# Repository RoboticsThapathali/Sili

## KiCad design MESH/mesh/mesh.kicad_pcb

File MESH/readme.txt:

//document created on 2019/20

contains two pcb layout
one of nano and other of arduino uno 
uno was tested 
but nano needs to be tested

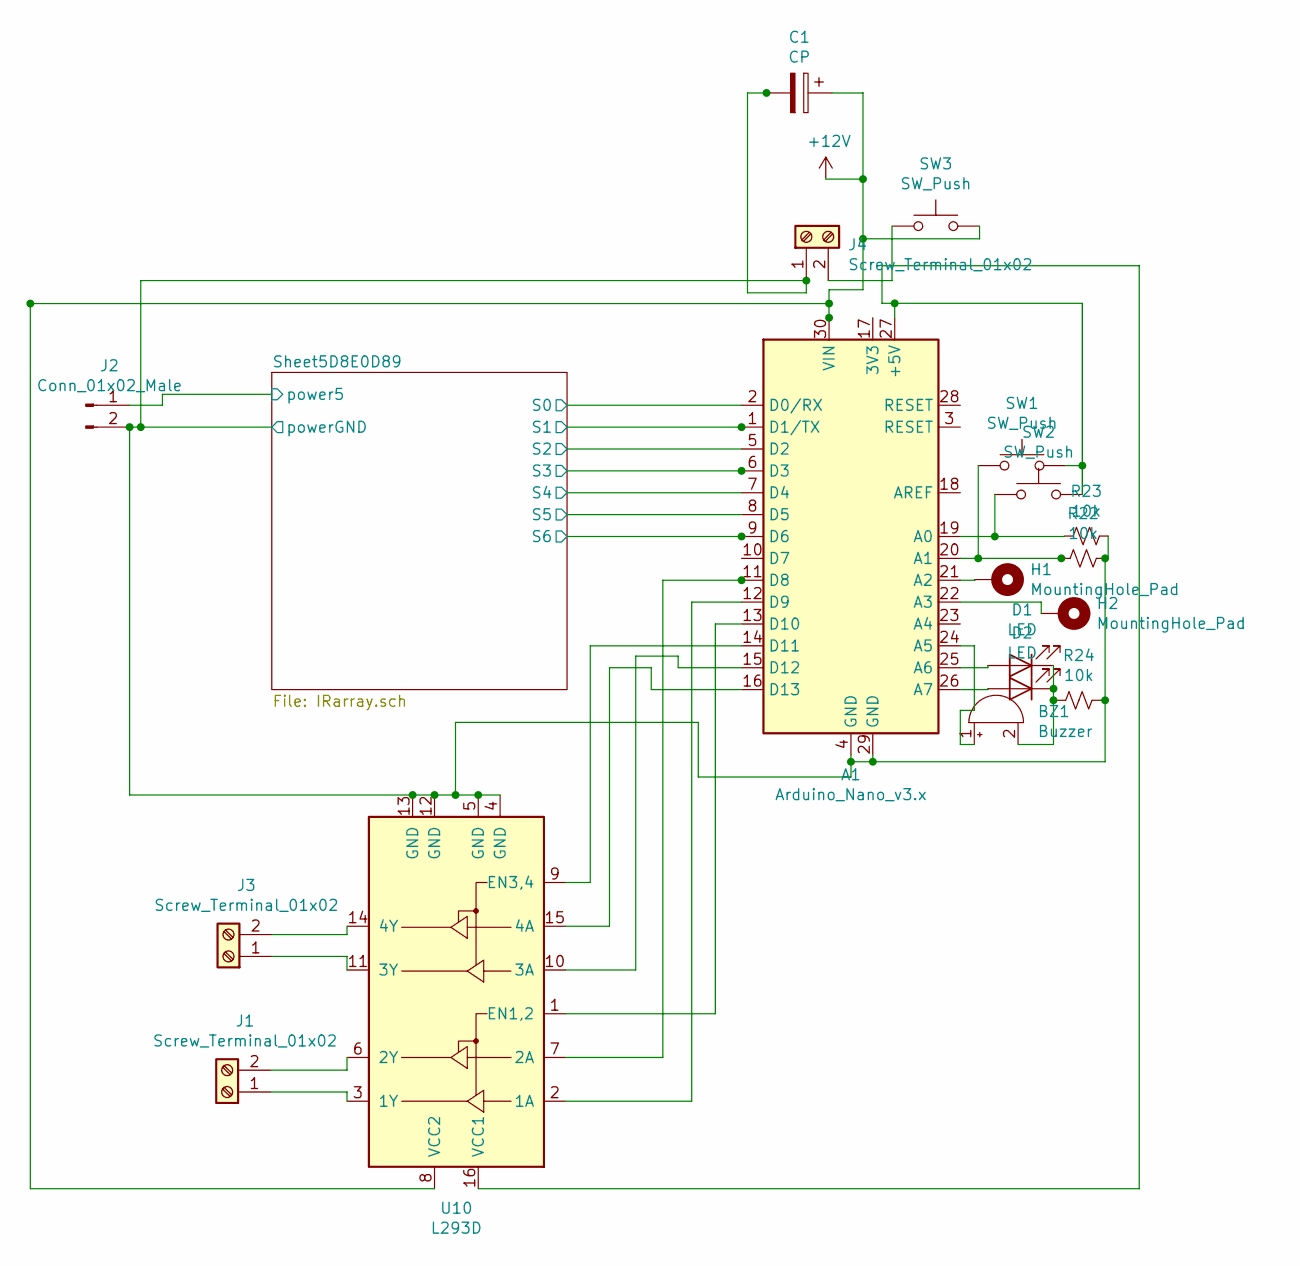
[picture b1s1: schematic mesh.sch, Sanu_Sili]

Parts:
A1: Arduino_Nano_v3.x; Arduino_Nano
BZ1: Buzzer; Buzzer_12x9.5RM7.6
C1: CP; CP_Radial_D8.0mm_P3.80mm
D1, D2: LED; LED_D5.0mm
H1, H2: MountingHole_Pad; MountingHole_4mm_Pad
J1, J3, J4: Screw_Terminal_01x02; TerminalBlock_Phoenix_MKDS-1,5-2-5.08_1x02_P5.08mm_Horizont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
J2: Conn_01x02_Male; PinHeader_1x02_P2.54mm_Vertical
R22, R23, R24: 10k; R_Axial_DIN0207_L6.3mm_D2.5mm_P7.62mm_Horizontal
SW1, SW2, SW3: SW_Push; SW_PUSH_6mm
U10: L293D; DIP-16_W7.62mm

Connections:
+12V: A1.30 (VIN), C1.1, SW3.2, U10.8 (VCC2)
/Sheet5D8E0D89/S0: A1.2 (D0/RX); also elsewhere on the board
/Sheet5D8E0D89/S1: A1.1 (D1/TX); also elsewhere on the board
/Sheet5D8E0D89/S2: A1.5 (D2); also elsewhere on the board
/Sheet5D8E0D89/S3: A1.6 (D3); also elsewhere on the board
/Sheet5D8E0D89/S4: A1.7 (D4); also elsewhere on the board
/Sheet5D8E0D89/S5: A1.8 (D5); also elsewhere on the board
/Sheet5D8E0D89/S6: A1.9 (D6); also elsewhere on the board
/Sheet5D8E0D89/power5: J2.1; also elsewhere on the board
/Sheet5D8E0D89/powerGND: A1.4 (GND), A1.29 (GND), C1.2, J2.2, J4.1, R22.1, R23.1, R24.1, U10.4 (GND), U10.5 (GND), U10.12 (GND), U10.13 (GND); also elsewhere on the board
unnamed: A1.11 (D8), U10.7 (2A)
unnamed: A1.12 (D9), U10.2 (1A)
unnamed: A1.13 (D10), U10.1 (EN1,2)
unnamed: A1.14 (D11), U10.9 (EN3,4)
unnamed: A1.15 (D12), U10.10 (3A)
unnamed: A1.16 (D13), U10.15 (4A)
unnamed: A1.19 (A0), R23.2, SW2.1
unnamed: A1.20 (A1), R22.2, SW1.1
unnamed: A1.21 (A2), H1.1
unnamed: A1.22 (A3), H2.1
unnamed: A1.24 (A5), BZ1.1 (-)
unnamed: A1.25 (A6), D1.2 (A)
unnamed: A1.26 (A7), D2.2 (A)
unnamed: A1.27 (+5V), SW1.2, SW2.2, U10.16 (VCC1)
unnamed: BZ1.2 (+), D1.1 (K), D2.1 (K), R24.2
unnamed: J1.1, U10.3 (1Y)
unnamed: J1.2, U10.6 (2Y)
unnamed: J3.1, U10.11 (3Y)
unnamed: J3.2, U10.14 (4Y)
unnamed: J4.2, SW3.1

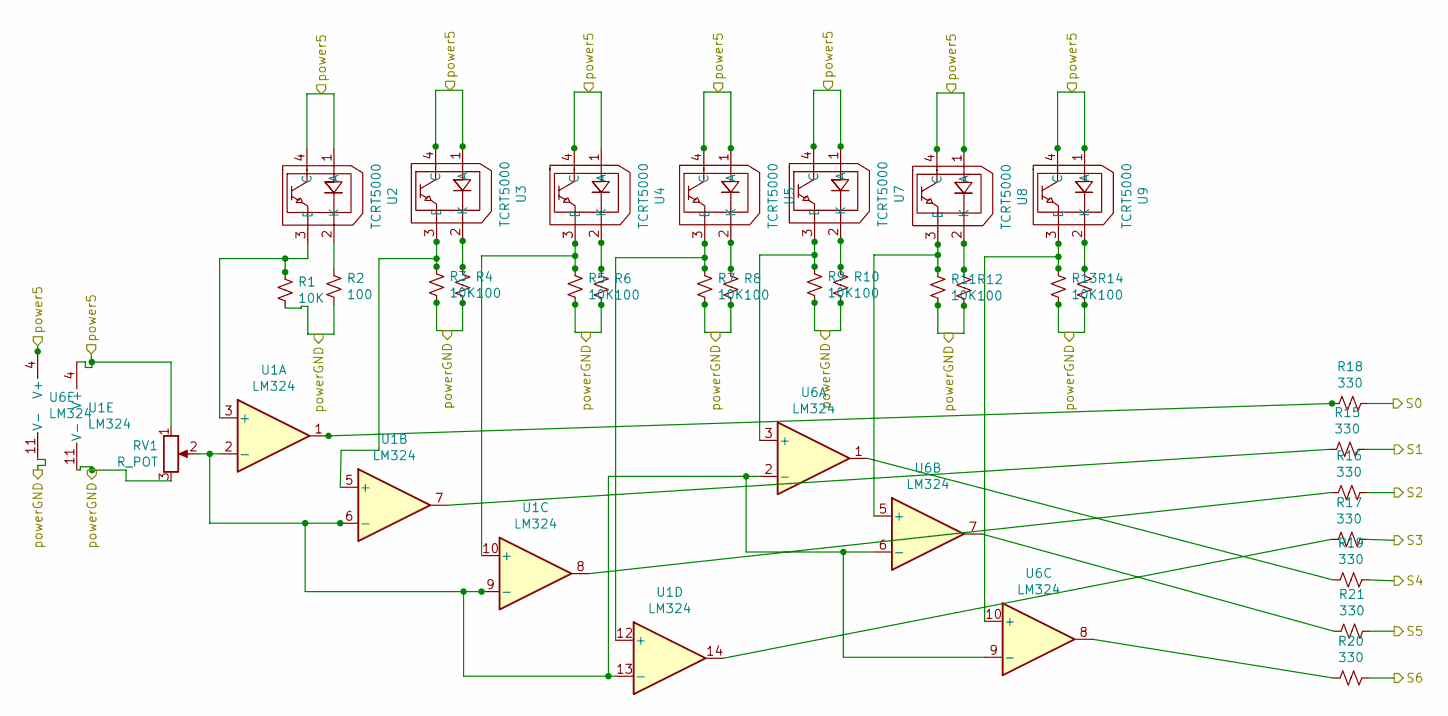
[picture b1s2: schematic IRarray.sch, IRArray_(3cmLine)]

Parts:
R1, R3, R5, R7, R9, R11, R13: 10K; R_Axial_DIN0207_L6.3mm_D2.5mm_P7.62mm_Horizontal
R2, R4, R6, R8, R10, R12, R14: 100; R_Axial_DIN0207_L6.3mm_D2.5mm_P7.62mm_Horizontal
R15, R16, R17, R18, R19, R20, R21: 330; R_Axial_DIN0207_L6.3mm_D2.5mm_P7.62mm_Horizontal
RV1: R_POT; Potentiometer_Runtron_RM-065_Vertical
U1, U6: LM324; DIP-14_W7.62mm
U2, U3, U4, U5, U7, U8, U9: TCRT5000; TCRT 5000

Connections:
/Sheet5D8E0D89/S0: R18.1; also elsewhere on the board
/Sheet5D8E0D89/S1: R15.1; also elsewhere on the board
/Sheet5D8E0D89/S2: R16.1; also elsewhere on the board
/Sheet5D8E0D89/S3: R17.1; also elsewhere on the board
/Sheet5D8E0D89/S4: R19.1; also elsewhere on the board
/Sheet5D8E0D89/S5: R21.1; also elsewhere on the board
/Sheet5D8E0D89/S6: R20.1; also elsewhere on the board
/Sheet5D8E0D89/power5: RV1.1, U1.4 (V+), U2.1 (A), U2.4 (C), U3.1 (A), U3.4 (C), U4.1 (A), U4.4 (C), U5.1 (A), U5.4 (C), U6.4 (V+), U7.1 (A), U7.4 (C), U8.1 (A), U8.4 (C), U9.1 (A), U9.4 (C); also elsewhere on the board
/Sheet5D8E0D89/powerGND: R1.2, R2.2, R3.2, R4.2, R5.2, R6.2, R7.2, R8.2, R9.2, R10.2, R11.2, R12.2, R13.2, R14.2, RV1.3, U1.11 (V-), U6.11 (V-); also elsewhere on the board
unnamed: R1.1, U1.3 (+), U2.3 (E)
unnamed: R2.1, U2.2 (K)
unnamed: R3.1, U1.5 (+), U3.3 (E)
unnamed: R4.1, U3.2 (K)
unnamed: R5.1, U1.10 (+), U4.3 (E)
unnamed: R6.1, U4.2 (K)
unnamed: R7.1, U1.12 (+), U5.3 (E)
unnamed: R8.1, U5.2 (K)
unnamed: R9.1, U6.3 (+), U7.3 (E)
unnamed: R10.1, U7.2 (K)
unnamed: R11.1, U6.5 (+), U8.3 (E)
unnamed: R12.1, U8.2 (K)
unnamed: R13.1, U6.10 (+), U9.3 (E)
unnamed: R14.1, U9.2 (K)
unnamed: R15.2, U1.7
unnamed: R16.2, U1.8
unnamed: R17.2, U1.14
unnamed: R18.2, U1.1
unnamed: R19.2, U6.1
unnamed: R20.2, U6.8
unnamed: R21.2, U6.7
unnamed: RV1.2, U1.2 (-), U1.6 (-), U1.9 (-), U1.13 (-), U6.2 (-), U6.6 (-), U6.9 (-)

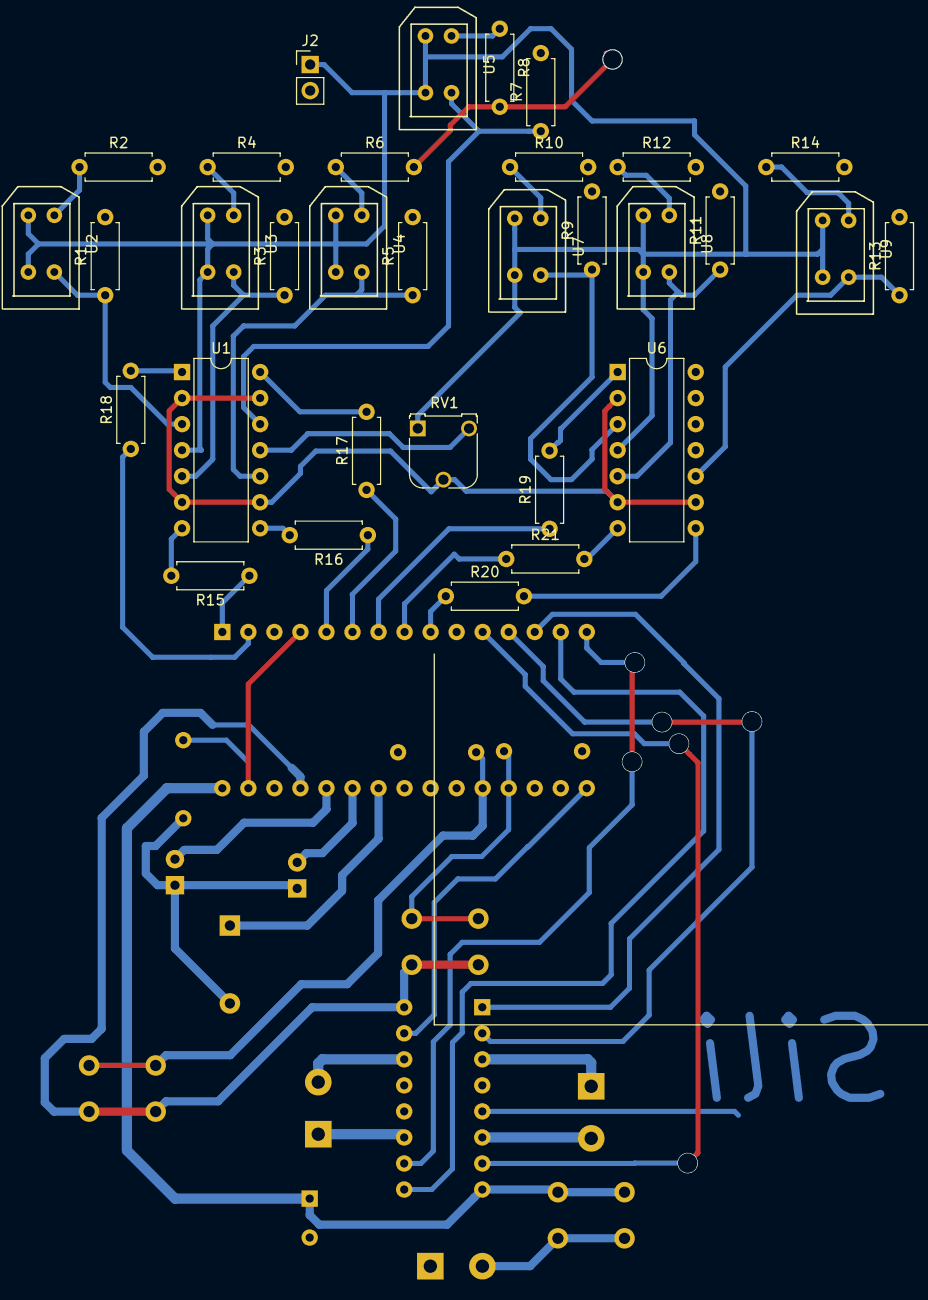
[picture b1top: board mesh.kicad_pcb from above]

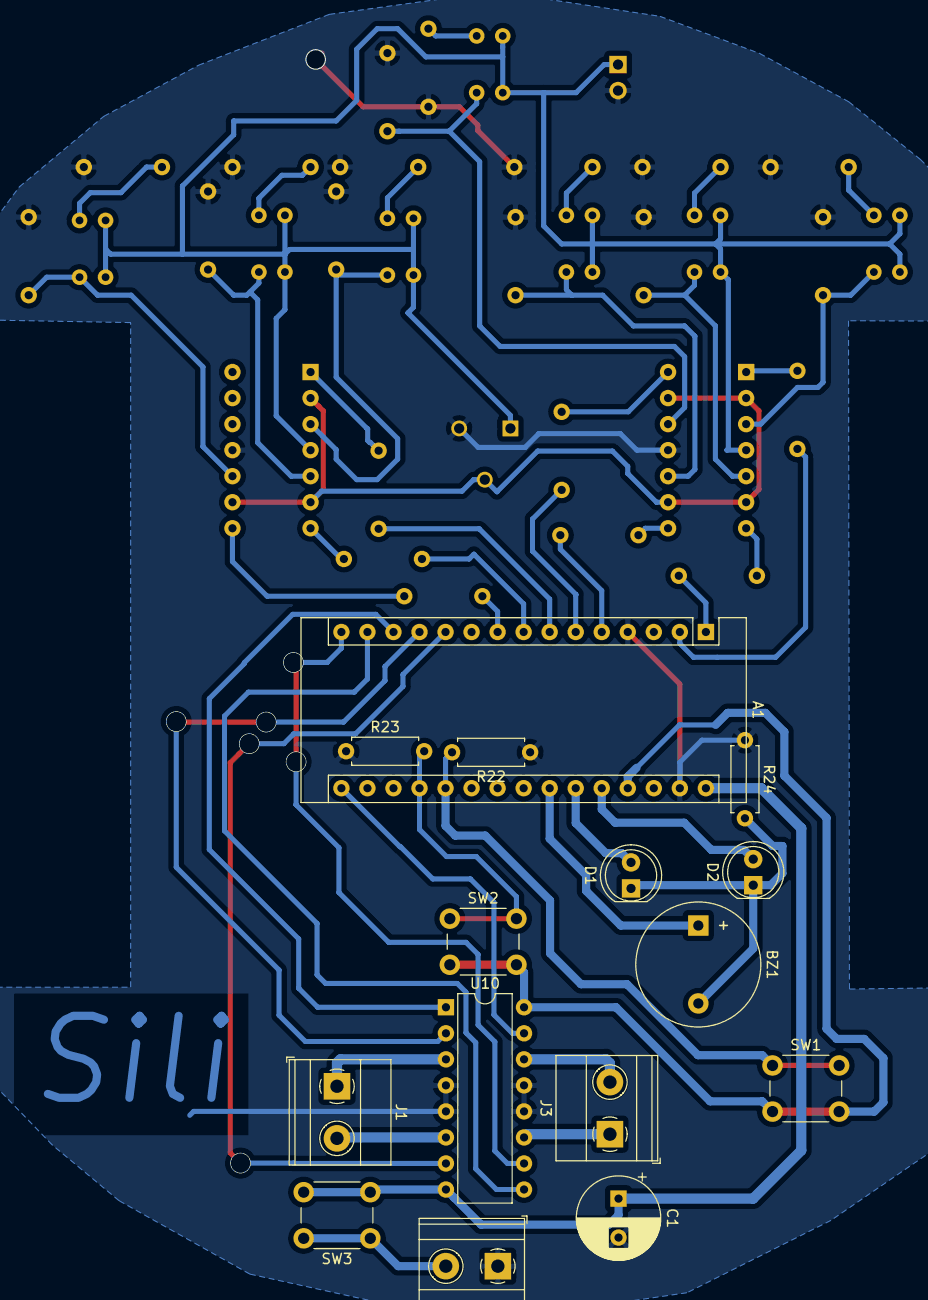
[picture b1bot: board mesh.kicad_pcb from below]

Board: 2 copper layers, 47 parts (15 on the bottom side), 50 nets.

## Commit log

2019-11-26 added code...
2019-11-26 contains info about the pcb printed
2019-11-26 documents
